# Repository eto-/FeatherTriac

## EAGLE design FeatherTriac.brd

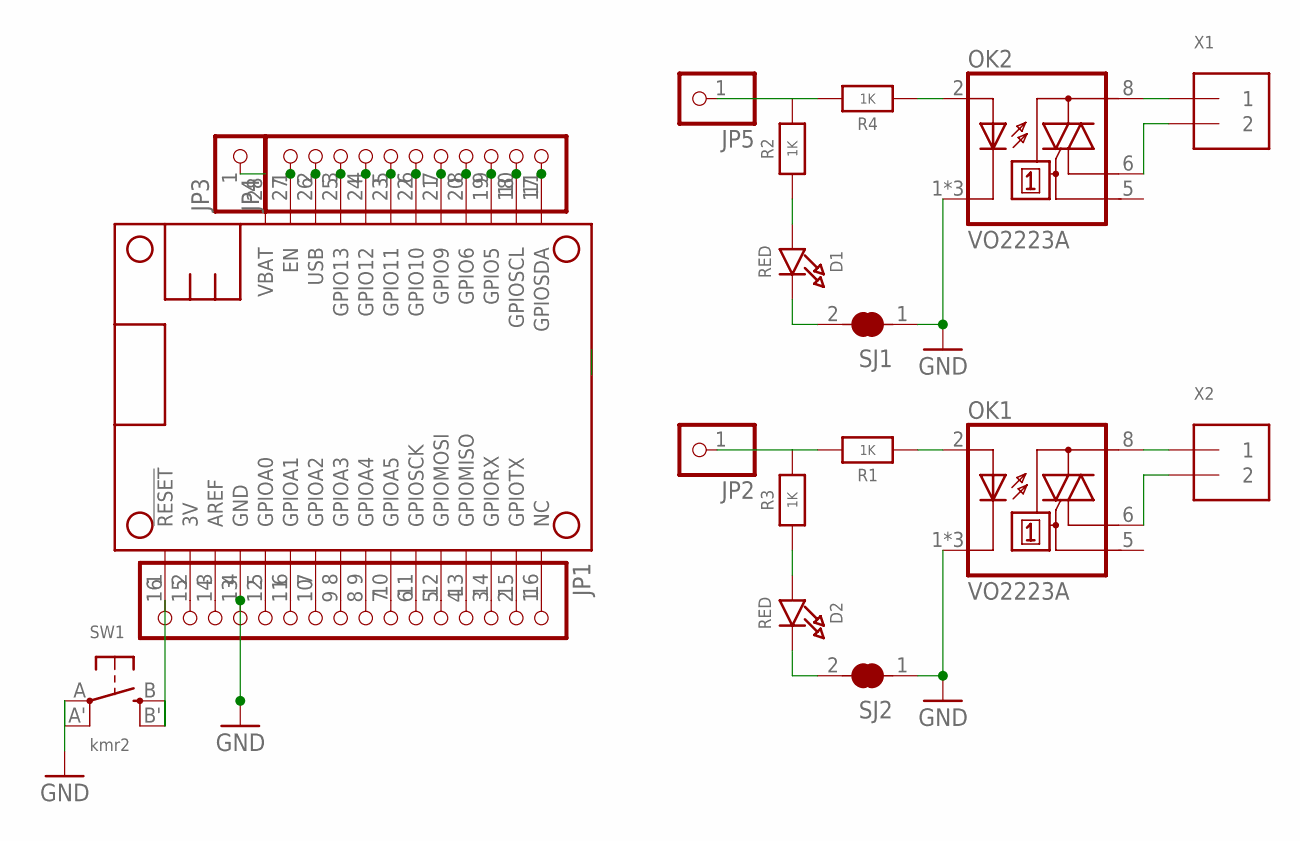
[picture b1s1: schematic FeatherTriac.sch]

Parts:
D1, D2: RED; CHIPLED_0805_NOOUTLINE
JP1: HEADER-1X16ROUND; 1X16_ROUND
JP2, JP3, JP5: HEADER-1X1ROUND; 1X01_ROUND
JP4: HEADER-1X11; 1X11_ROUND
MS1: MICROSHIELD
OK1, OK2: VO2223A; DIL7
R1, R2, R3, R4: 1K; 0805-NO
SJ1, SJ2: SOLDERJUMPER_CLOSED; SOLDERJUMPER_CLOSEDWIRE
SW1: kmr2; BTN_KMR2_4.6X2.8
X1, X2: TERMBLOCK_1X2; TERMBLOCK_1X2-3.5MM

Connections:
3V: JP1.15, MS1.2 (3V)
GND: JP1.13, MS1.4 (GND), OK1.1 (C), OK1.3 (C), OK1.4 (C), OK2.1 (C), OK2.3 (C), OK2.4 (C), SJ1.1, SJ2.1, SW1.A, SW1.A' (P1)
unnamed: D2.A, R3.1
unnamed: JP1.1, MS1.16 (NC)
unnamed: JP1.2, MS1.15 (GPIOTX)
unnamed: JP1.3, MS1.14 (GPIORX)
unnamed: JP1.4, MS1.13 (GPIOMISO)
unnamed: JP1.5, MS1.12 (GPIOMOSI)
unnamed: JP1.6, MS1.11 (GPIOSCK)
unnamed: JP1.7, MS1.10 (GPIOA5)
unnamed: JP1.8, MS1.9 (GPIOA4)
unnamed: JP1.9, MS1.8 (GPIOA3)
unnamed: JP1.10, MS1.7 (GPIOA2)
unnamed: JP1.11, MS1.6 (GPIOA1)
unnamed: JP1.12, MS1.5 (GPIOA0)
unnamed: JP4.1, MS1.27 (EN)
unnamed: JP4.3, MS1.25 (GPIO13)
unnamed: JP4.4, MS1.24 (GPIO12)
unnamed: JP4.5, MS1.23 (GPIO11)
unnamed: JP4.6, MS1.22 (GPIO10)
unnamed: JP4.7, MS1.21 (GPIO9)
unnamed: JP4.8, MS1.20 (GPIO6)
unnamed: JP4.9, MS1.19 (GPIO5)
unnamed: JP2.1, R1.2, R3.2
unnamed: JP1.14, MS1.3 (AREF)
unnamed: D2.C, SJ2.2
unnamed: OK1.2 (A), R1.1
unnamed: OK1.8 (T2), X2.1
unnamed: OK1.6 (T1), X2.2
unnamed: D1.A, R2.1
unnamed: OK2.2 (A), R4.1
unnamed: JP5.1, R2.2, R4.2
unnamed: D1.C, SJ1.2
unnamed: OK2.8 (T2), X1.1
unnamed: OK2.6 (T1), X1.2
RESET: JP1.16, MS1.1 (!RESET), SW1.B (S), SW1.B' (S1)
SCL: JP4.10, MS1.18 (GPIOSCL)
SDA: JP4.11, MS1.17 (GPIOSDA)
USB: JP4.2, MS1.26 (USB)
VBAT: JP3.1, MS1.28 (VBAT)

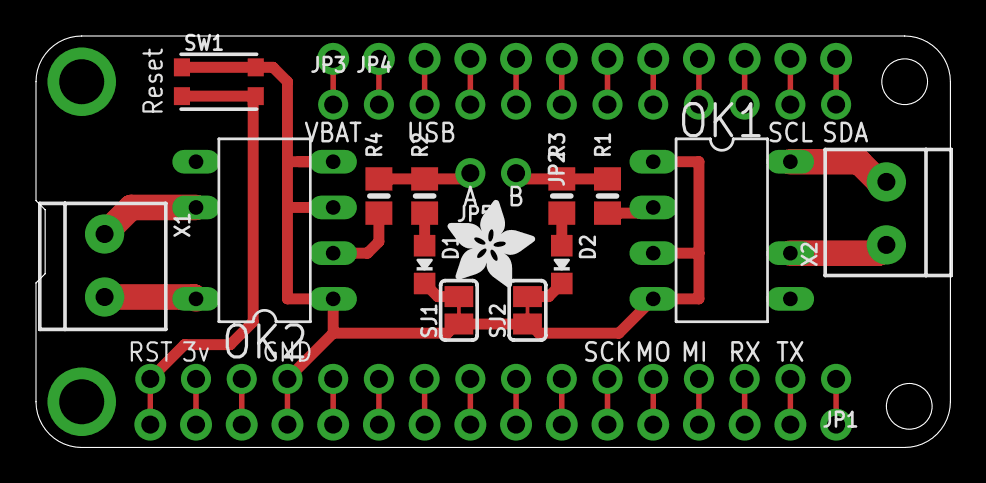
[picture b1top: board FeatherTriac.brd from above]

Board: 2 copper layers, 50.8 x 22.9 mm, 21 parts (1 on the bottom side), 40 nets.

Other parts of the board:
U$6: FEATHERLOGO
U$7: ADAFRUIT_5MM

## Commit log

2017-08-19 Added

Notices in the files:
parts and their libraries:
microbuilder: This work is placed in the public domain, and may be freely used for commercial and non-commercial work with the following conditions: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
